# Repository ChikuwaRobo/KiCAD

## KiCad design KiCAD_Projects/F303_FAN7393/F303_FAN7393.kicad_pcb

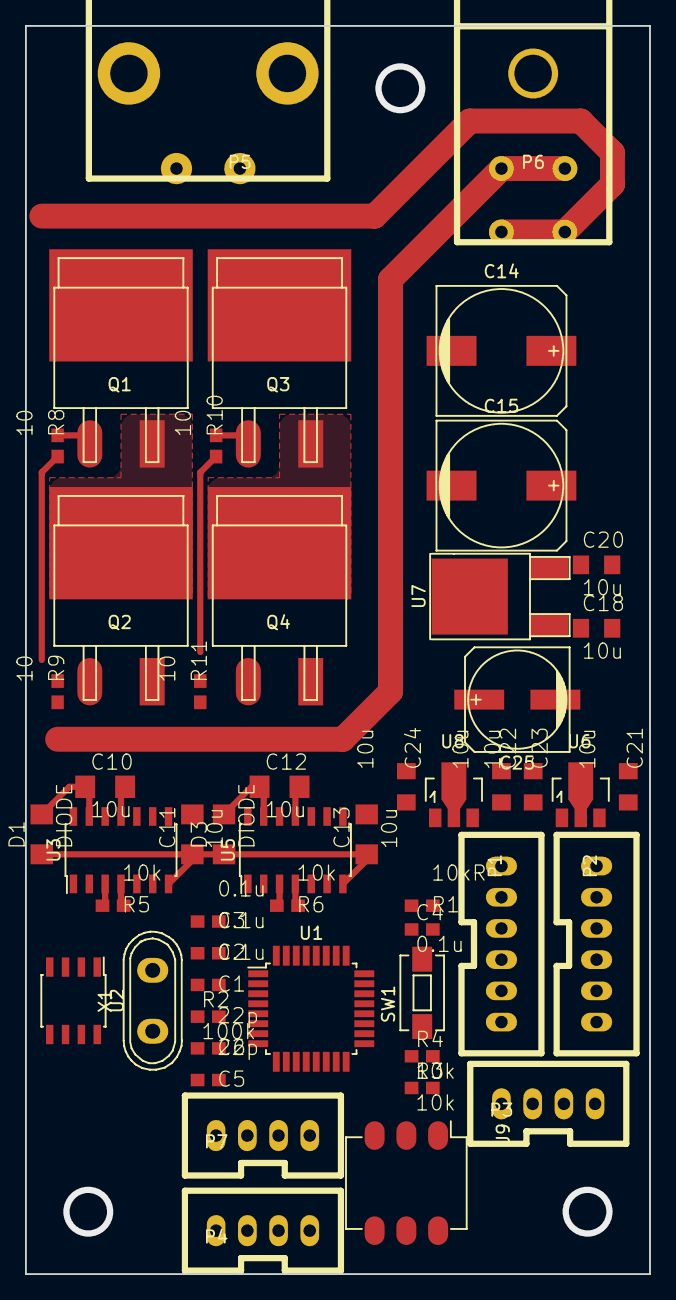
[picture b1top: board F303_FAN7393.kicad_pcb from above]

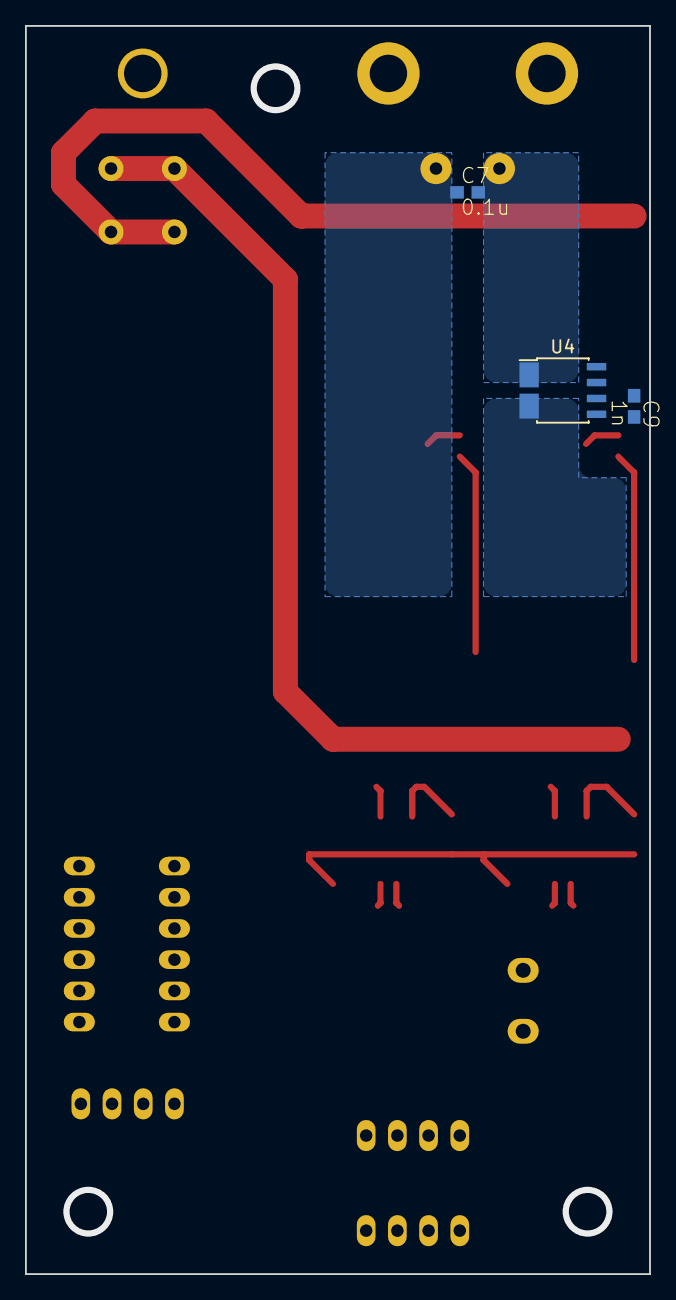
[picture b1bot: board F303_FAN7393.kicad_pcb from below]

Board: 2 copper layers, 50.0 x 100.0 mm, 55 parts (3 on the bottom side), 49 nets.

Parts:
C1, C2, C3, C4, C7: 0.1u; C1608
C5, C6: 22p; C1608
C9: 1n; C1608
C10, C11, C12, C13: 10u; C3216
C14, C15: 470u; c_elec_10x10.5
C18, C20, C21, C22, C23, C24: 10u; C2012
C25: 220u; c_elec_8x6.5
D1, D3: DIODE; C3216
P1, P2: CONN_01X06; XA_6T
P3, P4, P7: CONN_01X04; XA_4T
P5: CONN_01X02; D-3200S_2L
P6: CONN_01X04; D-3500D_4S
Q1, Q2, Q3, Q4: MOSFET_N; D2-PAK_GateEllipce
R1: 10kR; C1608
R2: 100k; C1608
R3, R4, R5, R6: 10k; C1608
R8, R9, R10, R11: 10; C1608
SW1: SW_PUSH; SW_SPST_EVQPE1
U1: STM32F303K8; TQFP-32_7x7mm_Pitch0.8mm
U2: MCP2551; SOIC-8_3.9x4.9mm_Pitch1.27mm
U3, U5: FAN7393; SOIC-14_3.9x8.7mm_Pitch1.27mm
U4: ACS714; SOIC-8_3.9x4.9mm_Pitch1.27mm_ACS
U6: NCP1117ST50T3G; SOT89-3_Housing
U7: MC78L15ACP; TO-252-2Lead
U8: NCP1117ST33T3G; SOT89-3_Housing
U9: SW_ROTARY_16
X1: CRYSTAL; Crystal_HC50-U_Vertical

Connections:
+3.3V: C1.1, C2.1, C3.1, C24.1, P1.2, R1.2, R3.1, R4.1, U1.1, U1.5, U1.17, U8.2
+5V: C22.1, C23.1, P3.2, U2.3, U4.8, U6.2, U8.3
+12V: P2.2, P4.2, P7.2
+BATT: C14.1, C15.1, C18.1, P6.2, P6.4, Q1.D, Q3.D, U7.1
/CAN_H: P4.4, P7.4, U2.7
/CAN_L: P4.3, P7.3, U2.6
/CAN_RX: U1.21, U2.4
/CAN_TX: U1.22, U2.1
/CURRENT_SENSE: U1.6, U4.7
/ENC_A: P3.3, P3.4, R3.2, R4.2, U1.27
/GD_PS: C11.1, C13.1, D1.1, D3.1, U3.7, U5.7
/GP_PS: C20.1, C21.1, C25.1, U6.3, U7.3
/OUT_A: C7.2, P5.2, U4.1, U4.2
/OUT_A_CS: C10.2, Q1.S, Q2.D, U3.11, U4.3, U4.4
/OUT_B: C7.1, C12.2, P5.1, Q3.S, Q4.D, U5.11
/PWM_A: U1.25, U3.1
/PWM_B: U1.26, U5.1
/ROTARY_1: U1.15, U9.1
/ROTARY_2: U1.18, U9.3
/ROTARY_4: U1.19, U9.4
/ROTARY_8: U1.20, U9.6
/SPI1_MISO/POT: P2.4, U1.12
/SPI1_MOSI: P2.3, U1.13
/SPI1_NSS/LIMIT_A: P2.6, U1.10
/SPI1_SCK/LIMIT_B: P2.5, U1.11
/USART1_RX: P1.6, U1.30
/USART1_TX: P1.5, U1.29
/~SD: U3.2, U5.2
GND: C1.2, C2.2, C3.2, C4.1, C5.2, C6.2, C9.2, C21.2, C22.2, C23.2, C24.2, P1.1, P2.1, P3.1, P4.1, P7.1, R2.1, R5.2, R6.2, SW1.1, U1.16, U1.31, U1.32, U2.2, U3.3, U4.5, U5.3, U6.1, U8.1, U9.2, U9.5
GNDPWR: C11.2, C13.2, C14.2, C15.2, C18.2, C20.2, C25.2, P6.1, P6.3, Q2.S, Q4.S, U3.5, U5.5, U7.2
unnamed: C4.2, R1.1, SW1.2, U1.4
unnamed: C5.1, U1.3, X1.1
unnamed: C6.1, U1.2, X1.2
unnamed: C9.1, U4.6
unnamed: C10.1, D1.2, U3.13
unnamed: C12.1, D3.2, U5.13
unnamed: P1.3, U1.24
unnamed: P1.4, U1.23
unnamed: Q1.G, R8.1
unnamed: Q2.G, R9.1
unnamed: Q3.G, R10.1
unnamed: Q4.G, R11.1
unnamed: R2.2, U2.8
unnamed: R5.1, U3.4
unnamed: R6.1, U5.4
unnamed: R8.2, U3.12
unnamed: R9.2, U3.6
unnamed: R10.2, U5.12
unnamed: R11.2, U5.6

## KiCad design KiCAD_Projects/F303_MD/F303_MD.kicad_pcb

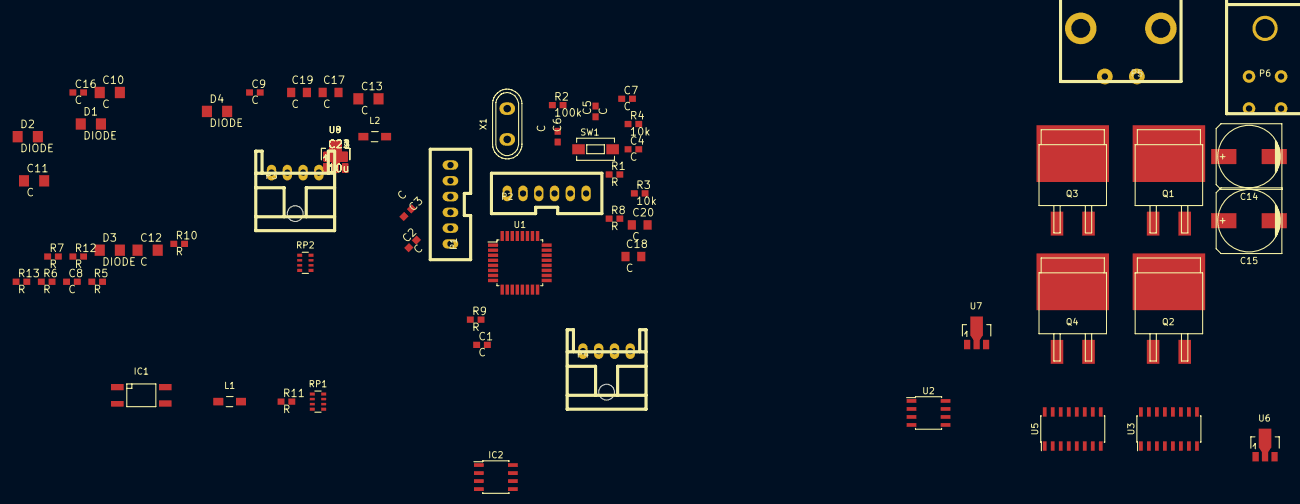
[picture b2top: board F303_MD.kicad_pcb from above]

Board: 2 copper layers, 68 parts (1 on the bottom side), 57 nets, no tracks yet.

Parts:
C1, C2, C3, C4, C5, C6, C7, C8, C9, C16: C; C1608
C10, C11, C12, C13: C; C3216
C14, C15: C; c_elec_10x10.5
C17, C18, C19, C20: C; C2012
C21, C22, C23, C24: 10u; C2012
D1, D2, D3, D4: DIODE; C3216
IC1: TLP785F; Optocoupler_SMD_HandSoldering_KPC357_LTV35x_PC357_SingleCha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
IC2: ATTINY85-P; SOIC-8_3.9x4.9mm_Pitch1.27mm
L1, L2: INDUCTOR_SMALL; Choke_SMD_1206_Standard
P1, P2: CONN_01X06; XA_6T
P3, P4: CONN_01X04; XA_4L
P5: CONN_01X02; D-3200S_2L
P6: CONN_01X04; D-3500D_4S
Q1, Q2, Q3, Q4: MOSFET_N; D2-PAK
R1, R5, R6, R7, R8, R9, R10, R11, R12, R13: R; C1608
R2: 100k; C1608
R3, R4: 10k; C1608
RP1, RP2: R_PACK4; R_Array_Convex_4x0603
SW1: SW_PUSH; SW_SPST_EVQPE1
U1: STM32F303K8; TQFP-32_7x7mm_Pitch0.8mm
U2: MCP2551; SOIC-8_3.9x4.9mm_Pitch1.27mm
U3, U5: SI8234; SOIC-16_3.9x9.9mm_Pitch1.27mm
U4: ACS714; SOIC-8_3.9x4.9mm_Pitch1.27mm
U6, U9: NCP1117ST50T3G; SOT89-3_Housing
U7: MC78L15ACP; SOT89-3_Housing
U8: NCP1117ST33T3G; SOT89-3_Housing
X1: CRYSTAL; Crystal_HC50-U_Vertical

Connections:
+3.3V: C1.1, C2.1, C3.1, C7.1, C8.1, C24.1, P1.2, R1.2, R3.1, R4.1, R7.1, U1.1, U1.5, U1.17, U3.3, U3.8, U5.3, U5.8, U8.2
+5V: C22.1, C23.1, P3.2, U2.3, U4.8, U6.2, U8.3
+12V: C21.1, P2.2, P4.2, U6.3
+BATT: C14.1, C15.1, L1.1, L2.1, P6.2, P6.4, Q1.D, Q3.D, RP1.4
/5V: C16.1, C19.1, IC2.8, U9.2
/CAN_RX: U1.21, U2.4
/CAN_TX: U1.22, U2.1
/ENC_A: P3.3, P3.4, R3.2, R4.2, U1.12
/GD_PS: D1.1, D2.1, D3.1, D4.1, RP1.1
/GP_PS: C20.1, U7.3
/OUT_A: P5.1, RP1.3, U4.3, U4.4
/OUT_A_CS: C10.2, Q1.S, Q2.D, U3.14, U4.1, U4.2
/OUT_B: C12.2, P5.2, Q3.S, Q4.D, RP1.2, U5.14
/PWM_A: U1.6, U3.1
/PWM_B: U1.7, U5.1
/SPI1_MISO: P2.4, U1.27
/SPI1_MOSI: P2.3, U1.28
/SPI1_NSS: P2.6, U1.25
/SPI1_SCK: P2.5, U1.26
/USART1_RX: P1.6, U1.30
/USART1_TX: P1.5, U1.29
/USART2_RX: IC1.4, R7.2, U1.9
/~EN: U1.10, U3.5, U5.5
GND: C1.2, C2.2, C3.2, C4.1, C5.2, C6.2, C7.2, C8.2, C9.2, C21.2, C22.2, C23.2, C24.2, IC1.3, P1.1, P2.1, P3.1, P4.1, R2.1, R5.2, R6.2, SW1.1, U1.16, U1.31, U1.32, U2.2, U3.4, U4.5, U5.4, U6.1, U8.1
GNDPWR: C11.2, C13.2, C14.2, C15.2, C16.2, C17.2, C18.2, C19.2, C20.2, IC1.2, IC2.4, P6.1, P6.3, Q2.S, Q4.S, RP2.5, RP2.6, RP2.7, RP2.8, U3.9, U5.9, U7.2, U9.1
unnamed: C4.2, R1.1, SW1.2, U1.4
unnamed: C5.1, U1.3, X1.1
unnamed: C6.1, U1.2, X1.2
unnamed: C9.1, U4.6
unnamed: C10.1, D1.2, U3.16
unnamed: C11.1, D2.2, U3.11
unnamed: C12.1, D3.2, U5.16
unnamed: C13.1, D4.2, U5.11
unnamed: C17.1, L1.2, U9.3
unnamed: C18.1, L2.2, U7.1
unnamed: IC1.1, R12.2
unnamed: IC2.1, R13.1
unnamed: IC2.2, RP1.5, RP2.4
unnamed: IC2.3, R12.1
unnamed: IC2.5, RP1.8, RP2.1
unnamed: IC2.6, RP1.7, RP2.2
unnamed: IC2.7, RP1.6, RP2.3
unnamed: P1.3, U1.24
unnamed: P1.4, U1.23
unnamed: P4.3, U2.6
unnamed: P4.4, U2.7
unnamed: Q1.G, R8.1
unnamed: Q2.G, R9.1
unnamed: Q3.G, R10.1
unnamed: Q4.G, R11.1
unnamed: R2.2, U2.8
unnamed: R5.1, U3.6
unnamed: R6.1, U5.6
unnamed: R8.2, U3.15
unnamed: R9.2, U3.10
unnamed: R10.2, U5.15
unnamed: R11.2, U5.10

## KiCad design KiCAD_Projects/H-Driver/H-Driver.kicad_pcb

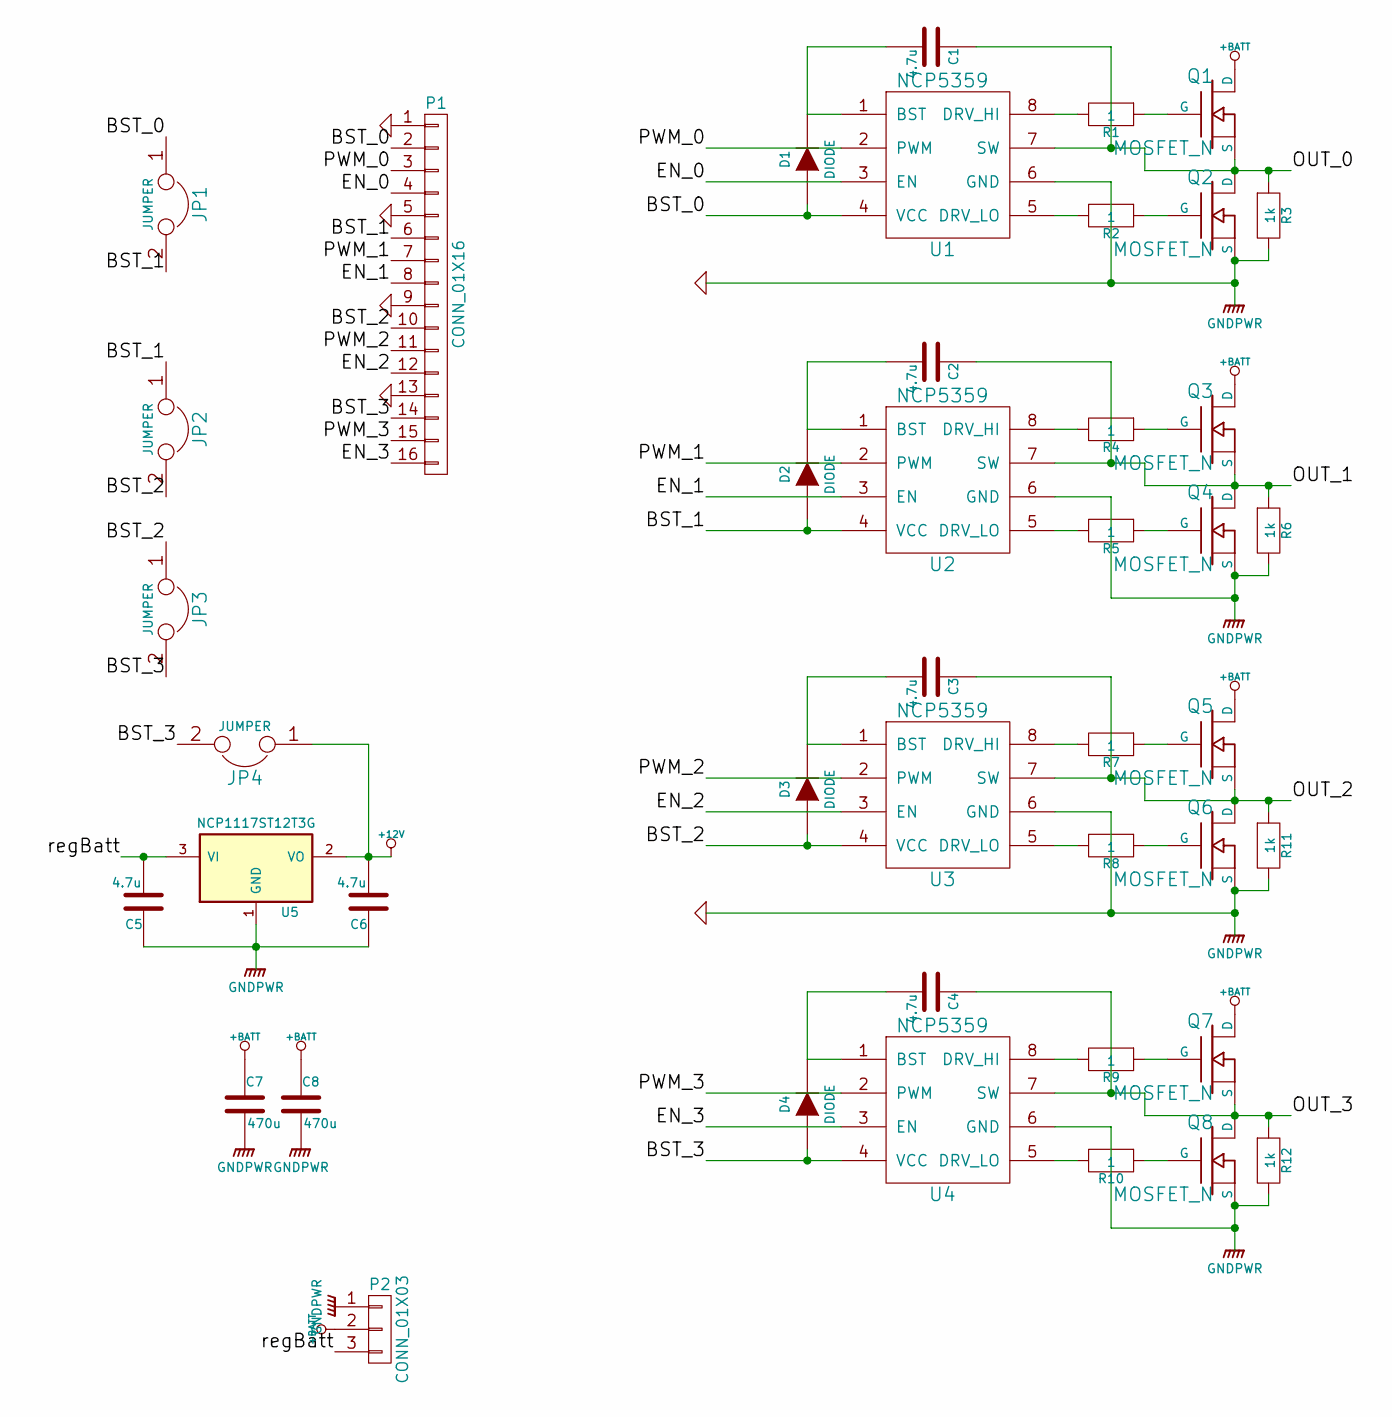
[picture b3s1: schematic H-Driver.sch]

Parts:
C1, C2, C3, C4, C5, C6: 4.7u; C3216_S
C7, C8: 470u; C_Radial_D10_L13_P5
D1, D2, D3, D4: DIODE; C1608_WP_S
JP1, JP2, JP3, JP4: JUMPER; GS2
P1: CONN_01X16; Pin_Header_Straight_1x16
P2: CONN_01X03; Pin_Header_Straight_1x03
Q1, Q2, Q3, Q4, Q5, Q6, Q7, Q8: MOSFET_N; SOT-428_GDS_compact
R1, R2, R4, R5, R7, R8, R9, R10: 1; C1608_WP_S
R3, R6, R11, R12: 1k; C1608_WP_S
U1, U2, U3, U4: NCP5359; SOIC-8_3.9x4.9mm_Pitch1.27mm_S
U5: NCP1117ST12T3G; SOT-223_reg

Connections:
+12V: C6.2, JP4.1, U5.2 (VO)
+BATT: C7.1, C8.1, P2.2, Q1.D, Q3.D, Q5.D, Q7.D
/BST_0: D1.2 (A), JP1.1, P1.2, U1.4 (VCC)
/BST_1: D2.2 (A), JP1.2, JP2.1, P1.6, U2.4 (VCC)
/BST_2: D3.2 (A), JP2.2, JP3.1, P1.10, U3.4 (VCC)
/BST_3: D4.2 (A), JP3.2, JP4.2, P1.14, U4.4 (VCC)
/EN_0: P1.4, U1.3 (EN)
/EN_1: P1.8, U2.3 (EN)
/EN_2: P1.12, U3.3 (EN)
/EN_3: P1.16, U4.3 (EN)
/OUT_0: C1.1, Q1.S, Q2.D, R3.1, U1.7 (SW)
/OUT_1: C2.1, Q3.S, Q4.D, R6.1, U2.7 (SW)
/OUT_2: C3.1, Q5.S, Q6.D, R11.1, U3.7 (SW)
/OUT_3: C4.1, Q7.S, Q8.D, R12.1, U4.7 (SW)
/PWM_0: P1.3, U1.2 (PWM)
/PWM_1: P1.7, U2.2 (PWM)
/PWM_2: P1.11, U3.2 (PWM)
/PWM_3: P1.15, U4.2 (PWM)
/regBatt: C5.2, P2.3, U5.3 (VI)
GND: C5.1, C6.1, C7.2, C8.2, P1.1, P1.5, P1.9, P1.13, P2.1, Q2.S, Q4.S, Q6.S, Q8.S, R3.2, R6.2, R11.2, R12.2, U1.6 (GND), U2.6 (GND), U3.6 (GND), U4.6 (GND), U5.1 (GND)
unnamed: C1.2, D1.1 (K), U1.1 (BST)
unnamed: C2.2, D2.1 (K), U2.1 (BST)
unnamed: C3.2, D3.1 (K), U3.1 (BST)
unnamed: C4.2, D4.1 (K), U4.1 (BST)
unnamed: Q1.G, R1.1
unnamed: Q2.G, R2.1
unnamed: Q3.G, R4.1
unnamed: Q4.G, R5.1
unnamed: Q5.G, R7.1
unnamed: Q6.G, R8.1
unnamed: Q7.G, R9.1
unnamed: Q8.G, R10.1
unnamed: R1.2, U1.8 (DRV_HI)
unnamed: R2.2, U1.5 (DRV_LO)
unnamed: R4.2, U2.8 (DRV_HI)
unnamed: R5.2, U2.5 (DRV_LO)
unnamed: R7.2, U3.8 (DRV_HI)
unnamed: R8.2, U3.5 (DRV_LO)
unnamed: R9.2, U4.8 (DRV_HI)
unnamed: R10.2, U4.5 (DRV_LO)

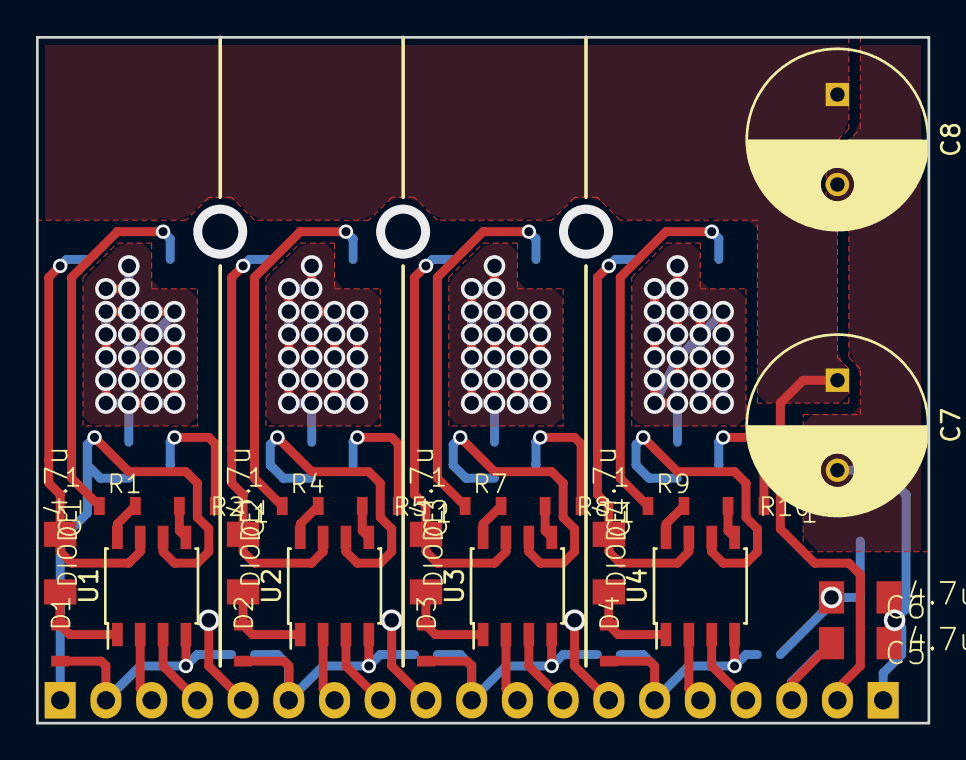
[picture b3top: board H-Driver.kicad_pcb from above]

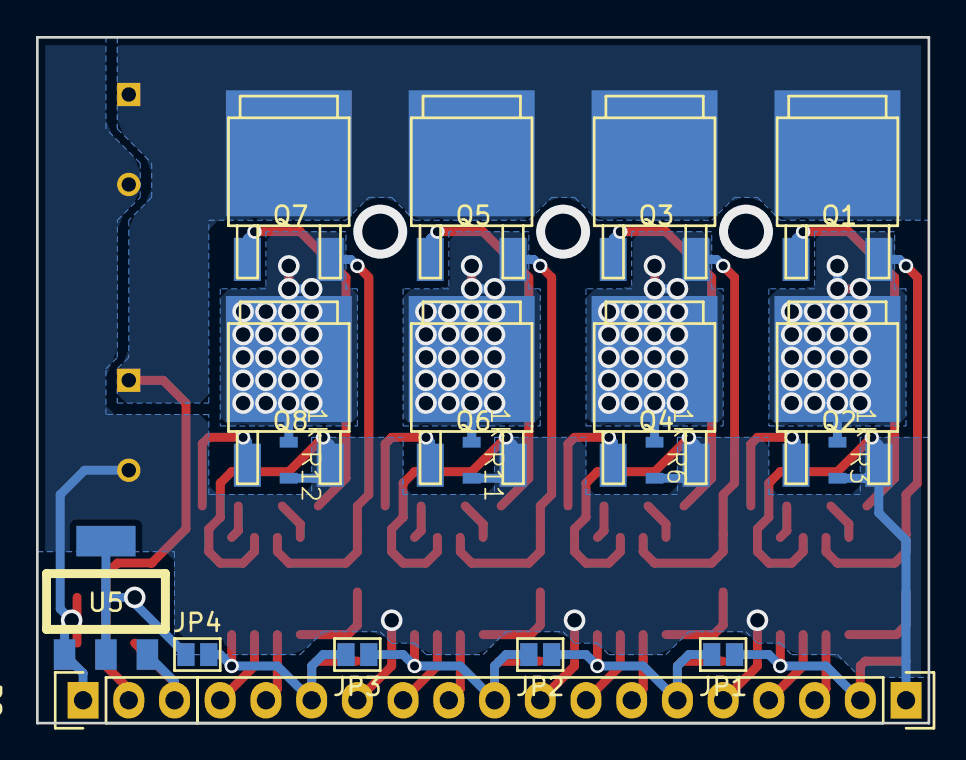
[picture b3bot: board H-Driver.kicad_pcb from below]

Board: 2 copper layers, 49.5 x 38.1 mm, 43 parts (19 on the bottom side), 40 nets.

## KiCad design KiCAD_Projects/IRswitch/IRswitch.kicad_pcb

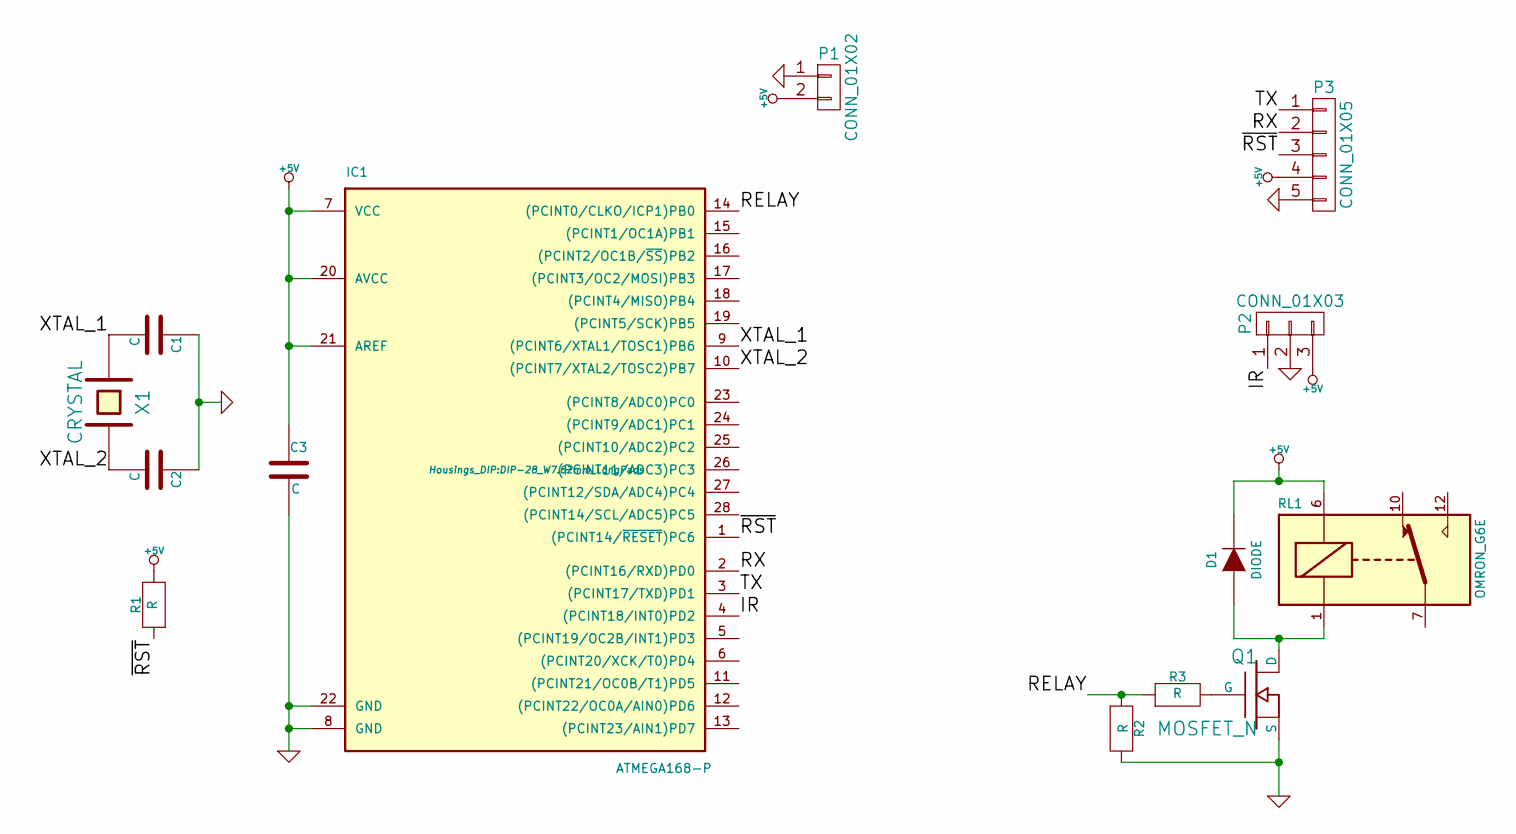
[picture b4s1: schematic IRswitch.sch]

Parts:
C1, C2, C3: C; C2012
D1: DIODE; 0204_2f7
IC1: ATMEGA168-P; DIP-28_W7.62mm_LongPads
P1: CONN_01X02; XA_2T
P2: CONN_01X03; Pin_Header_Straight_1x03
P3: CONN_01X05; Pin_Header_Angled_1x05
Q1: MOSFET_N; SOT-23_Handsoldering
R1, R2, R3: R; 0204_2f7
RL1: OMRON_G6E; Relay_SPDS_OMRON-G6E
X1: CRYSTAL; Crystal_HC49-U_Vertical

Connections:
+5V: C3.1, D1.2 (K), IC1.7 (VCC), IC1.20 (AVCC), IC1.21 (AREF), P1.2, P2.3, P3.4, R1.2, RL1.6
/IR: IC1.4 ((PCINT18/INT0)PD2), P2.1
/RELAY: IC1.14 ((PCINT0/CLKO/ICP1)PB0), R2.1, R3.1
/RX: IC1.2 ((PCINT16/RXD)PD0), P3.2
/TX: IC1.3 ((PCINT17/TXD)PD1), P3.1
/XTAL_1: C1.2, IC1.9 ((PCINT6/XTAL1/TOSC1)PB6), X1.1
/XTAL_2: C2.2, IC1.10 ((PCINT7/XTAL2/TOSC2)PB7), X1.2
/~RST: IC1.1 ((PCINT14/~RESET~)PC6), P3.3, R1.1
GND: C1.1, C2.1, C3.2, IC1.8 (GND), IC1.22 (GND), P1.1, P2.2, P3.5, Q1.S, R2.2
unnamed: D1.1 (A), Q1.D, RL1.1
unnamed: Q1.G, R3.2

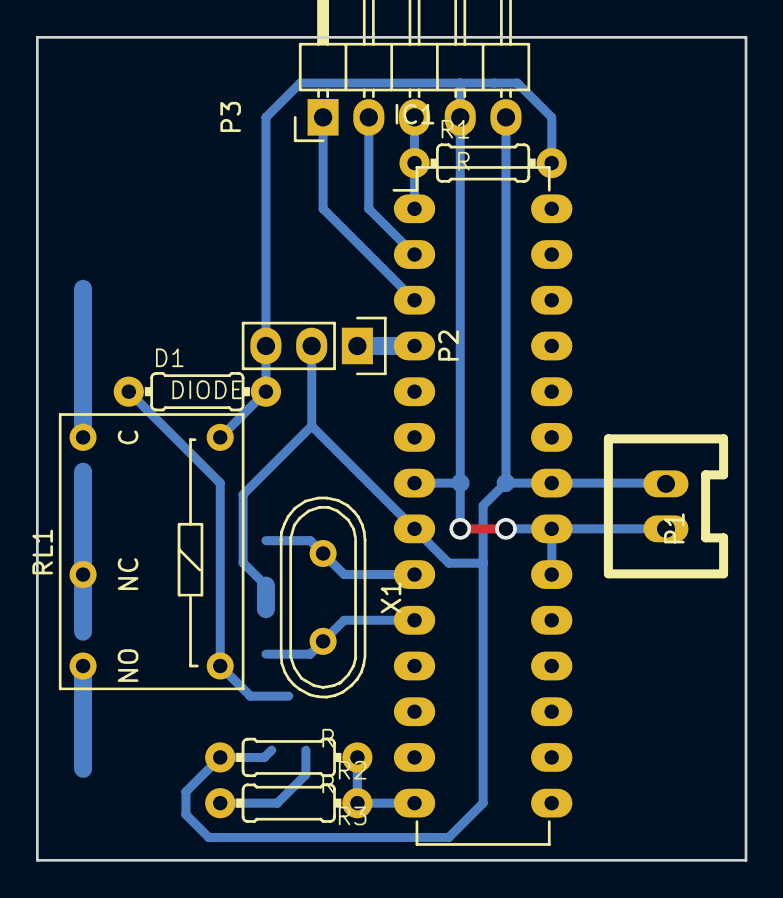
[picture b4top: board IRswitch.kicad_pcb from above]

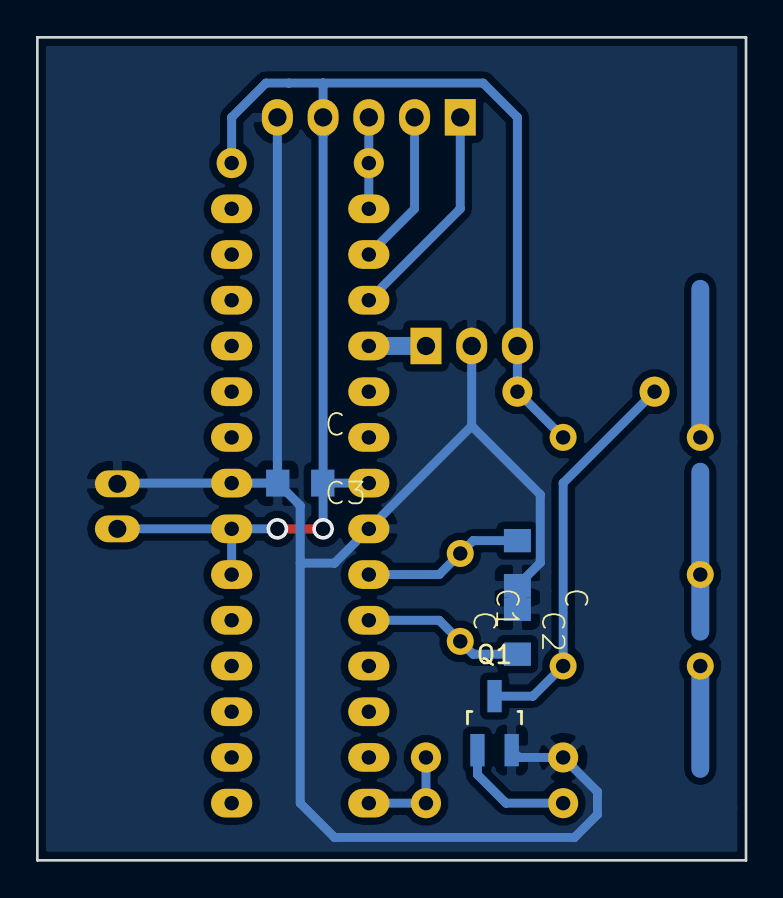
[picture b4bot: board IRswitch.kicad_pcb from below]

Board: 2 copper layers, 39.4 x 45.7 mm, 14 parts (4 on the bottom side), 11 nets.

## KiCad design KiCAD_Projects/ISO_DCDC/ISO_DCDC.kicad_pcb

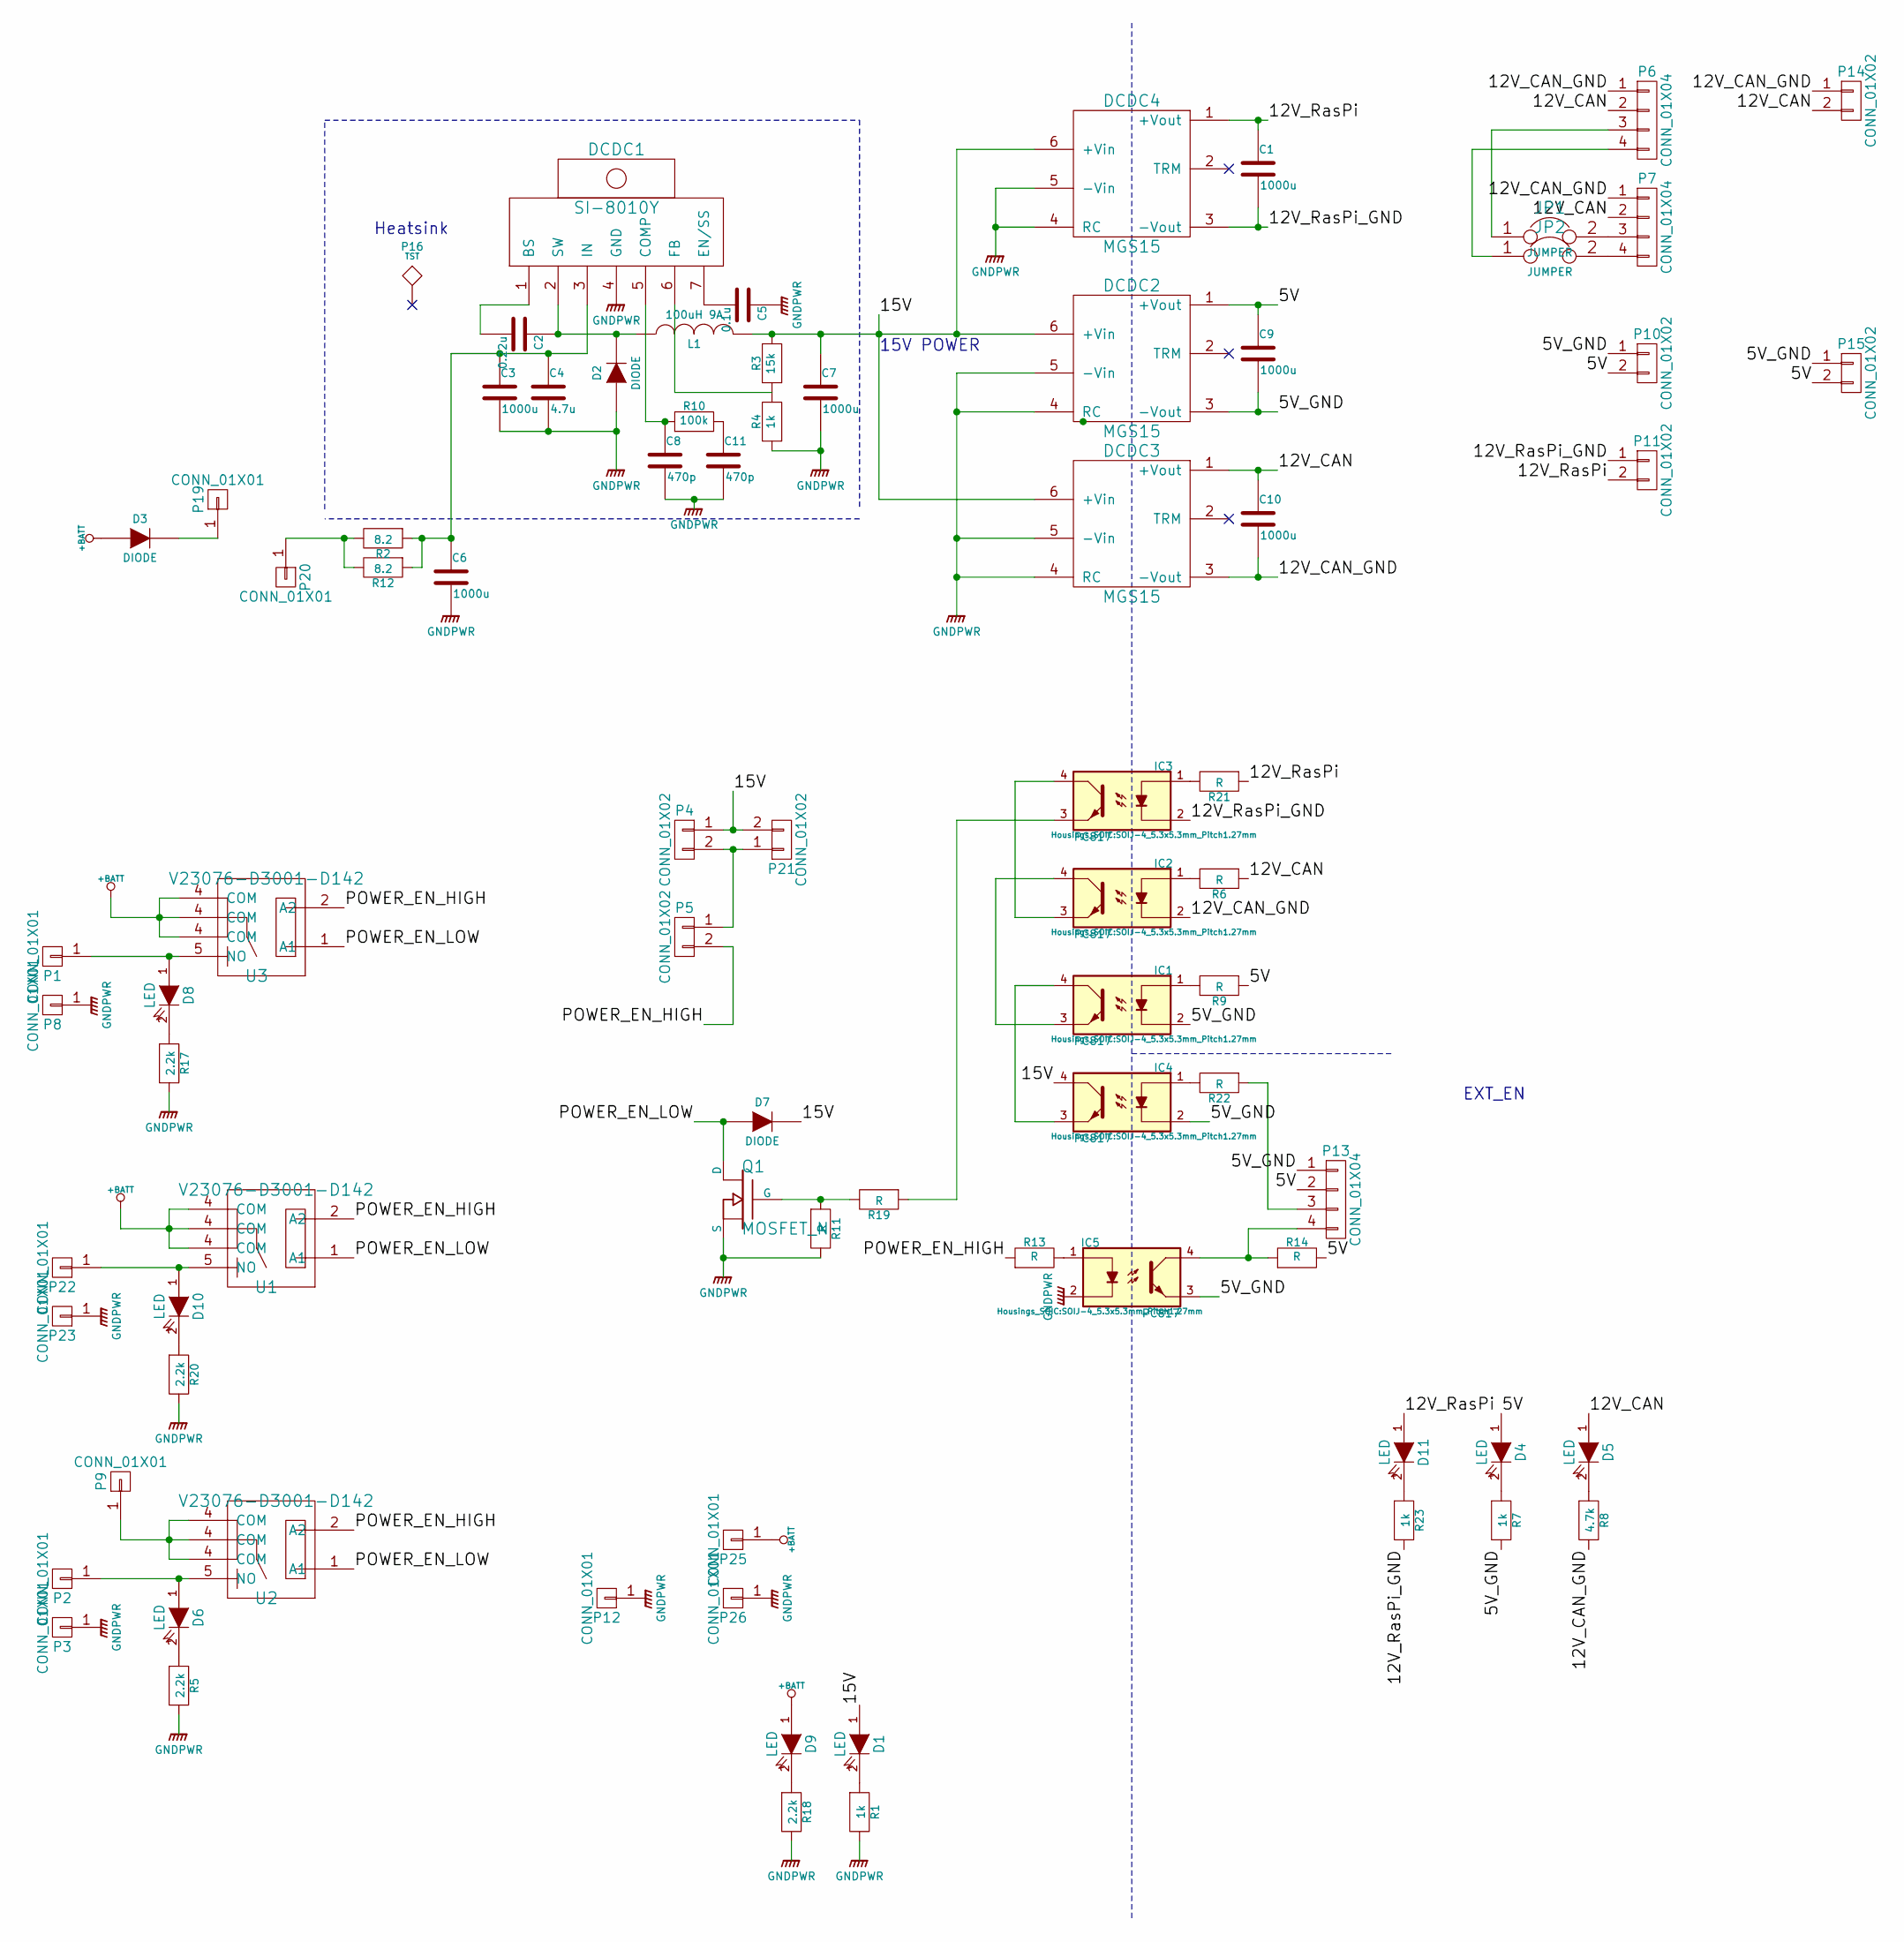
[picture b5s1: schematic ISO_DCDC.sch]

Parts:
C1, C9, C10: 1000u; C_Radial_D8_L11.5_P3.5
C2: 0.22u; C1608_WP
C3, C6, C7: 1000u; C_Radial_D10_L20_P5
C4: 4.7u; C3216
C5: 0.1u; C1608_WP
C8, C11: 470p; C1608_WP
D1, D4, D5, D6, D8, D9, D10, D11: LED; LED-3MM
D2, D3: DIODE; POWER_DI5
D7: DIODE; C3216
DCDC1: SI-8010Y; TO-220_7_Vertical
DCDC2, DCDC3: MGS15
DCDC4: MGS15; MGS30
IC1, IC2, IC3, IC4, IC5: PC817; SOIJ-4_5.3x5.3mm_Pitch1.27mm
JP1, JP2: JUMPER; Pin_Header_Straight_1x02
L1: 100uH 9A; Choke_Toroid_8.5x24mm_Vertical
P1, P2, P3, P8, P9, P12, P19, P20, P22, P23, P25, P26: CONN_01X01; 1pin
P4, P5: CONN_01X02; XA_2LC
P6, P7: CONN_01X04; XA_4T
P10, P11, P14, P15: CONN_01X02; XA_2T
P13: CONN_01X04; XA_4LC
P16: TST; 16PB017_16.25.16
P21: CONN_01X02; Pin_Header_Straight_1x02
Q1: MOSFET_N; SOT-23_Handsoldering
R1, R4, R7, R23: 1k; C1608_WP
R2, R12: 8.2; R_2512
R3: 15k; C1608_WP
R5, R17, R18, R20: 2.2k; C1608_WP
R6, R9, R11, R14, R21, R22: R; C1608_WP
R8: 4.7k; C1608_WP
R10: 100k; C1608_WP
R13, R19: R; 0204_2f5
U1, U2, U3: V23076-D3001-D142; V23076-A3001-D142

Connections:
+BATT: D3.2 (A), D9.1 (A), P25.1, U1.4 (COM), U3.4 (COM)
/5V: C9.1, D4.1 (A), DCDC2.1 (+Vout), P10.2, P13.2, P15.2, R9.1, R14.2
/5V_GND: C9.2, DCDC2.3 (-Vout), IC1.2, IC4.2, IC5.3, P10.1, P13.1, P15.1, R7.2
/12V_CAN: C10.1, D5.1 (A), DCDC3.1 (+Vout), P6.2, P7.2, P14.2, R6.1
/12V_CAN_GND: C10.2, DCDC3.3 (-Vout), IC2.2, P6.1, P7.1, P14.1, R8.2
/12V_RasPi: C1.1, D11.1 (A), DCDC4.1 (+Vout), P11.2, R21.1
/12V_RasPi_GND: C1.2, DCDC4.3 (-Vout), IC3.2, P11.1, R23.2
/15V: C7.1, D1.1 (A), D7.1 (K), DCDC2.6 (+Vin), DCDC3.6 (+Vin), DCDC4.6 (+Vin), IC4.4, L1.2, P4.1, P21.2, R3.2
/POWER_EN_HIGH: P5.2, R13.1, U1.2 (A2), U2.2 (A2), U3.2 (A2)
/POWER_EN_LOW: D7.2 (A), Q1.D, U1.1 (A1), U2.1 (A1), U3.1 (A1)
GNDPWR: C3.2, C4.2, C5.1, C6.2, C7.2, C8.2, C11.2, D2.2 (A), DCDC1.4 (GND), DCDC2.4 (RC), DCDC2.5 (-Vin), DCDC3.4 (RC), DCDC3.5 (-Vin), DCDC4.4 (RC), DCDC4.5 (-Vin), IC5.2, P3.1, P8.1, P12.1, P23.1, P26.1, Q1.S, R1.2, R4.1, R5.2, R11.2, R17.2, R18.2, R20.2
unnamed: C2.1, D2.1 (K), DCDC1.2 (SW), L1.1
unnamed: C2.2, DCDC1.1 (BS)
unnamed: C3.1, C4.1, C6.1, DCDC1.3 (IN), R2.1, R12.1
unnamed: C5.2, DCDC1.7 (EN/SS)
unnamed: C8.1, DCDC1.5 (COMP), R10.1
unnamed: C11.1, R10.2
unnamed: D1.2 (K), R1.1
unnamed: D3.1 (K), P19.1
unnamed: D4.2 (K), R7.1
unnamed: D5.2 (K), R8.1
unnamed: D6.1 (A), P2.1, U2.5 (NO)
unnamed: D6.2 (K), R5.1
unnamed: D8.1 (A), P1.1, U3.5 (NO)
unnamed: D8.2 (K), R17.1
unnamed: D9.2 (K), R18.1
unnamed: D10.1 (A), P22.1, U1.5 (NO)
unnamed: D10.2 (K), R20.1
unnamed: D11.2 (K), R23.1
unnamed: DCDC1.6 (FB), R3.1, R4.2
unnamed: IC1.1, R9.2
unnamed: IC1.3, IC2.4
unnamed: IC1.4, IC4.3
unnamed: IC2.1, R6.2
unnamed: IC2.3, IC3.4
unnamed: IC3.1, R21.2
unnamed: IC3.3, R19.1
unnamed: IC4.1, R22.2
unnamed: IC5.1, R13.2
unnamed: IC5.4, P13.4, R14.1
unnamed: JP1.1, P6.3
unnamed: JP1.2, P7.3
unnamed: JP2.1, P6.4
unnamed: JP2.2, P7.4
unnamed: P9.1, U2.4 (COM)
unnamed: P13.3, R22.1
unnamed: P20.1, R2.2, R12.2
unnamed: P4.2, P5.1, P21.1
unnamed: Q1.G, R11.1, R19.2

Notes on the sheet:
15V POWER
EXT_EN
Heatsink
